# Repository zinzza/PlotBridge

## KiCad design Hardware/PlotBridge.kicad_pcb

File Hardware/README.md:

# PlotBridge — KiCad 프로젝트

ESP32-C3 SuperMini · ST7789 1.69" LCD · MAX3232(4핀) 모듈을 얹는 **캐리어 보드**다.
세 모듈 모두 완제품을 헤더에 꽂는 구조라 이 기판에는 능동소자가 없다.

보드는 **70 × 45 mm, 2층, 배선 완료** 상태다. ERC·DRC 모두 0건이다.

## 파일

| 파일 | 내용 |
|---|---|
| `PlotBridge.kicad_pro` | 프로젝트 파일 — KiCad에서 이걸 연다 |
| `PlotBridge.kicad_sch` | 회로도 (심볼 내장, 외부 라이브러리 불필요) |
| `PlotBridge.kicad_pcb` | 보드 — 외곽 70×45 mm, 부품 배치, 넷, **배선 완료**, M3 홀 4개 |
| `PlotBridge-schematic.pdf` | 회로도 출력본 |
| `PlotBridge.kicad_sym` | 심볼 라이브러리 |
| `PlotBridge.pretty/` | 풋프린트 라이브러리 (`.kicad_mod` 4종) |
| `sym-lib-table` / `fp-lib-table` | 프로젝트 로컬 라이브러리 등록 |
| `tools/` | 이 프로젝트를 생성·검증한 스크립트 |

## 검증 결과

KiCad 10.0.5의 `kicad-cli` / `pcbnew`로 실제 실행한 결과다.

| 항목 | 결과 | 도구 |
|---|---|---|
| ERC (회로도) | **0 violations** | `kicad-cli sch erc` |
| DRC (보드) | **0 violations** | `kicad-cli pcb drc` |
| 미연결 패드 | **0** | 〃 |
| 보드 패드↔넷 vs 회로도 넷리스트 | 10/10 넷 일치 | `tools/verify_board.py` |
| 심볼 핀번호 ↔ 풋프린트 패드 위치 | 28/28 일치 | `tools/verify_fp.py` |
| 같은 층 다른 넷 교차(단락) | **0** | `tools/verify_cross.py` |

## 넷리스트

| 넷 | ESP32-C3 | 상대 | 배선층 |
|---|---|---|---|
| `+3V3` | 3V3 (pin 6) | LCD VCC, MAX3232 VCC | B.Cu |
| `GND` | GND (pin 7) | LCD GND, MAX3232 GND | B.Cu |
| `LCD_SCL` | GPIO4 | LCD SCL | B.Cu |
| `LCD_SDA` | GPIO6 | LCD SDA | F.Cu |
| `LCD_RST` | GPIO1 | LCD RES | F.Cu |
| `LCD_DC` | GPIO3 | LCD DC | B.Cu |
| `LCD_CS` | GPIO2 | LCD CS | B.Cu |
| `LCD_BL` | GPIO5 | LCD BLK | B.Cu |
| `UART_TX` | GPIO0 | MAX3232 RX | B.Cu |
| `UART_RX` | GPIO7 | MAX3232 TX | F.Cu |

미사용: `5V`, `GPIO10`, `GPIO20`, `GPIO21` (no-connect 처리).
`GPIO8`(내장 LED), `GPIO9`(BOOT 버튼)는 모듈 온보드라 기판에서 연결하지 않는다.

## 배치와 배선

| 부품 | 위치 | 방향 |
|---|---|---|
| U1 ESP32-C3 SuperMini | (45, 47.5) | 세로, USB-C가 위 |
| U2 ST7789 LCD | (70, 47.5) | 세로 8핀, U1 오른쪽 |
| U3 MAX3232 | (45, 63) | **가로 4핀, U1 아래** (90° 회전) |
| H1–H4 M3 홀 | 네 모서리 | — |

U3는 왼쪽부터 `VCC(41.19) · GND(43.73) · RX(46.27) · TX(48.81)` 순으로 놓인다.

B.Cu가 주 배선층이다 — 모듈 본체가 윗면에 있어 아랫면이 통째로 비어 있고,
U1의 두 패드 열 사이 공간도 양면 모두 자유롭게 쓸 수 있다. 서로 교차하는
3개 넷(`LCD_SDA`, `LCD_RST`, `UART_RX`)만 F.Cu로 올렸다. 관통(THT) 패드가
양면을 잇기 때문에 **비아는 하나도 없다.** 트랙 폭 0.25 mm.

---

# 설계 노트

작업하면서 실제로 확인하거나 판단한 것들을 남긴다.

## ESP32-C3 SuperMini 핀 배치 — 가장 주의할 점

풋프린트는 **윗면(부품면) 기준, USB-C가 −Y 방향**이다. 이 기준에서 **전원핀은 오른쪽**이다.

| 왼쪽 열 (위→아래) | 오른쪽 열 (위→아래) |
|---|---|
| GPIO5, 6, 7, 8, 9, 10, 20, 21 | 5V, GND, 3V3, GPIO4, 3, 2, 1, 0 |

웹에 널리 퍼진 **"전원이 왼쪽"** 핀아웃 그림은 **뒷면(bottom) 뷰**가 앞면으로 잘못
재배포된 것이다. 이 그림을 그대로 믿고 기판을 뜨면 좌우가 뒤집힌 보드가 나온다.

실물 확인법(10초): USB-C를 위로 두고 칩이 보이는 면에서, 아래쪽 실크에
**왼쪽 `21` / 오른쪽 `0`** 이 찍혀 있으면 맞다.

근거는 세 갈래다.
- 독립 KiCad 라이브러리 6종이 모두 같은 배치(패드 좌표에 신호명이 직접 박혀 있어 해석 여지 없음)
- 실물 보드 실크스크린 사진
- Tenstar(AliExpress) 구매품 실물 확인

## 빨강/파랑 선이 겹쳐 보이는데 괜찮은가

괜찮다. 빨강은 `F.Cu`(윗면 동박), 파랑은 `B.Cu`(아랫면 동박)이고 사이에는
**1.6 mm 두께의 FR4 기판**이 있다. 도면에서 겹쳐 보이는 건 위에서 내려다본
투영일 뿐, 실제로는 육교와 그 아래 도로처럼 만나지 않는다. 2층 기판을 쓰는 이유가
바로 이것이다.

문제가 되는 건 **같은 층에서 다른 넷이 교차**하는 경우다. `tools/verify_cross.py`가
트랙 42개의 모든 쌍을 계산해 분류한다.

| 분류 | 개수 | |
|---|---|---|
| F.Cu ↔ B.Cu 교차 | 13 | 다른 층 — 무해 |
| 같은 층, 같은 넷 접촉 | 32 | 의도된 것 (모서리·분기) |
| **같은 층, 다른 넷 교차** | **0** | 단락 없음 |
| **같은 층, 다른 넷 간격 0.2 mm 미만** | **0** | 규칙 위반 없음 |

## 2층이면 1층보다 비싼가

**아니다. 소량에서는 오히려 2층이 더 싸거나 같다.**

요즘 PCB 업체의 표준 제품이 양면(2층)이다. 단면(1층)은 별도 옵션으로 없거나, 있어도
같은 값이거나, 비표준 공정이라 더 비싸다. 단가표의 기준 가격 자체가 2층이다.

단면이 실제로 싸지는 건 **수천 장 단위 양산**에서 FR-1/CEM-1 같은 저가 기판재를
쓸 때다. 리모컨이나 저가 완구 기판이 그 경우다. 시제품 5~10장에는 해당 없다.

이 보드는 70 × 45 mm라 대부분 업체의 최저가 구간(100 × 100 mm 이하)에 넉넉히 들어간다.

굳이 1층으로 내리려면 F.Cu를 쓰는 3개 넷(`LCD_SDA`, `LCD_RST`, `UART_RX`)을
점퍼선이나 0옴 저항으로 공중 배선해야 한다. 가격 이득 없이 조립 수고와 실수 여지만
늘어나므로 권하지 않는다.

## 수작업 납땜이 가능한가

가능하다. 난이도로 치면 가장 쉬운 축이다.

**층수는 납땜 난이도와 무관하다.** 층수는 제조사가 하는 일이고, 난이도를 좌우하는 건
부품 패키지와 패드 크기다. 오히려 공장에서 만든 2층 기판은 홀 내벽에 구리가 도금되어
나오므로(PTH, plated through-hole), **한쪽 면만 납땜해도 납이 구멍을 타고 올라가
양쪽 층이 자동으로 연결**된다. 윗면에 따로 손댈 필요가 없다.
(집에서 직접 에칭한 2층 기판이라면 양면 납땜이 필요하지만, 발주 기판은 해당 없다.)

| 항목 | 값 | 평가 |
|---|---|---|
| 부품 | 전부 THT (핀헤더) | SMD 0개 |
| 패드 지름 | 1.8 mm | 넉넉함 |
| 드릴 | 1.0 mm | 2.54 mm 헤더 핀(0.64 mm 각)에 여유 |
| 애뉼러 링 | 0.4 mm | 인두 팁 닿을 면적 충분 |
| 인접 패드 간격 | 0.74 mm | 브리지 위험 낮음 |
| 납땜할 핀 | 28개 (16+8+4) | — |

### 조립 순서

1. **암 헤더(female header)를 기판에 먼저 납땜한다.** 모듈이 올라가면 인두가 안 들어간다.
2. 납땜은 **아랫면(B.Cu)에서만** 하면 된다.
3. 모듈 3개를 나중에 꽂는다.

암 헤더를 쓰면 모듈을 뺐다 꽂을 수 있다. MAX3232 핀 순서가 다른 제품으로 바꿔야 할
때를 대비해서도 소켓 방식이 안전하다.

인두는 320~350 °C에 핀당 2~3초면 충분하다.

## KiCad와 EasyEDA

둘 다 무료로 시작할 수 있지만 성격이 다르다.

| | KiCad | EasyEDA |
|---|---|---|
| 라이선스 | 완전 무료·오픈소스(GPL), 기능 제한 없음 | 웹 버전 무료, 비공개 프로젝트 개수 제한 |
| 유료 등급 | 없음 | EasyEDA Pro (데스크톱) |
| 강점 | 어느 제조사에나 통하는 범용 거버 출력 | JLCPCB 부품 소싱·주문 연동 |

이 프로젝트는 KiCad를 골랐다. 국내 업체(devicemart 등)에 거버로 넘기기에 무난하고,
특정 제조사 생태계에 묶이지 않기 때문이다.

## PCB 발주에 필요한 것

발주 페이지가 요구하는 건 배선도(개념 회로도)가 아니라 실제 동박 패턴이 담긴
**거버(Gerber) 파일**과 드릴 파일이다. `Docs/wiring_diagram.html`은 연결 관계를
보여주는 문서일 뿐 발주용이 아니다.

```bash
kicad-cli pcb export gerbers --output gerber/ PlotBridge.kicad_pcb
kicad-cli pcb export drill   --output gerber/ PlotBridge.kicad_pcb
```

---

# 제작 전 확인 사항

1. **MAX3232 모듈의 핀 순서를 실물로 확인한다.** 4핀 모듈은 판매자마다 순서가 다르다.
   현재 풋프린트는 `VCC, GND, RX, TX` (pin 1 = VCC) 기준이다.
2. MAX3232 모듈이 **3.3V VCC**를 지원하는지 확인한다. 5V 전용이면 레벨 변환이 필요하다.
3. RS-232 측은 모듈의 DB9 커넥터를 쓴다. 이 기판에는 RS-232 신호가 올라오지 않는다.
   플로터 연결은 교차: MAX3232 TX → 플로터 RX, MAX3232 RX ← 플로터 TX.
4. LCD 모듈의 8핀 순서(`GND VCC SCL SDA RES DC CS BLK`)도 실물 실크와 대조한다.
5. LCD(1.69")와 MAX3232 모듈의 **실제 외형이 서로 간섭하지 않는지** 확인한다.
   현재 배치는 헤더 간격만 기준이며 모듈 본체 크기는 반영하지 않았다.

---

# 재생성

`tools/gen_kicad.py`가 회로도·보드·라이브러리를 전부 생성한다. 배치나 배선을 바꾸려면
스크립트의 `PLACE` / `ROUTES`를 고치고 다시 돌린다.

`tools/normalize_pcb.py`는 KiCad 자체 엔진(`pcbnew`)으로 보드의 모든 풋프린트를
라이브러리에서 다시 불러와 같은 자리에 재배치한다. 손으로 쓴 사본은 부품을 **회전**시키는
순간 라이브러리와 어긋나므로(KiCad는 풋프린트 텍스트 각도를 보드 절대각으로 저장한다)
이 단계가 없으면 DRC가 `lib_footprint_mismatch`를 낸다. KiCad 번들 파이썬으로 돌린다.

```bash
python tools/gen_kicad.py
"C:/Program Files/KiCad/10.0/bin/python.exe" tools/normalize_pcb.py
python tools/verify_net.py && python tools/verify_fp.py && python tools/verify_board.py
python tools/verify_cross.py
```

검증기는 서로 독립적이다.

| 스크립트 | 확인하는 것 |
|---|---|
| `verify_net.py` | 회로도 기하학에서 넷리스트를 재구성해 의도와 대조 |
| `verify_fp.py` | 심볼 핀번호 ↔ 풋프린트 패드 물리 위치 |
| `verify_board.py` | 보드의 패드↔넷이 회로도와 일치하는지 |
| `verify_cross.py` | 같은 층에서 다른 넷이 닿는 곳이 있는지 |

DRC는 보드가 "자기모순이 없음"만 보장하지 "맞다"는 것은 보장하지 않는다. 넷을 잘못
할당해도 DRC는 통과한다. 그래서 위 대조가 따로 필요하다.

> **주의:** 재생성은 `.kicad_sch` / `.kicad_pcb`를 덮어쓴다. KiCad에서 프로젝트를 열어둔
> 상태로 돌렸다면, KiCad를 닫았다가 다시 열어야 새 내용이 보인다. 열린 창에서 저장하면
> 재생성한 내용이 지워진다.

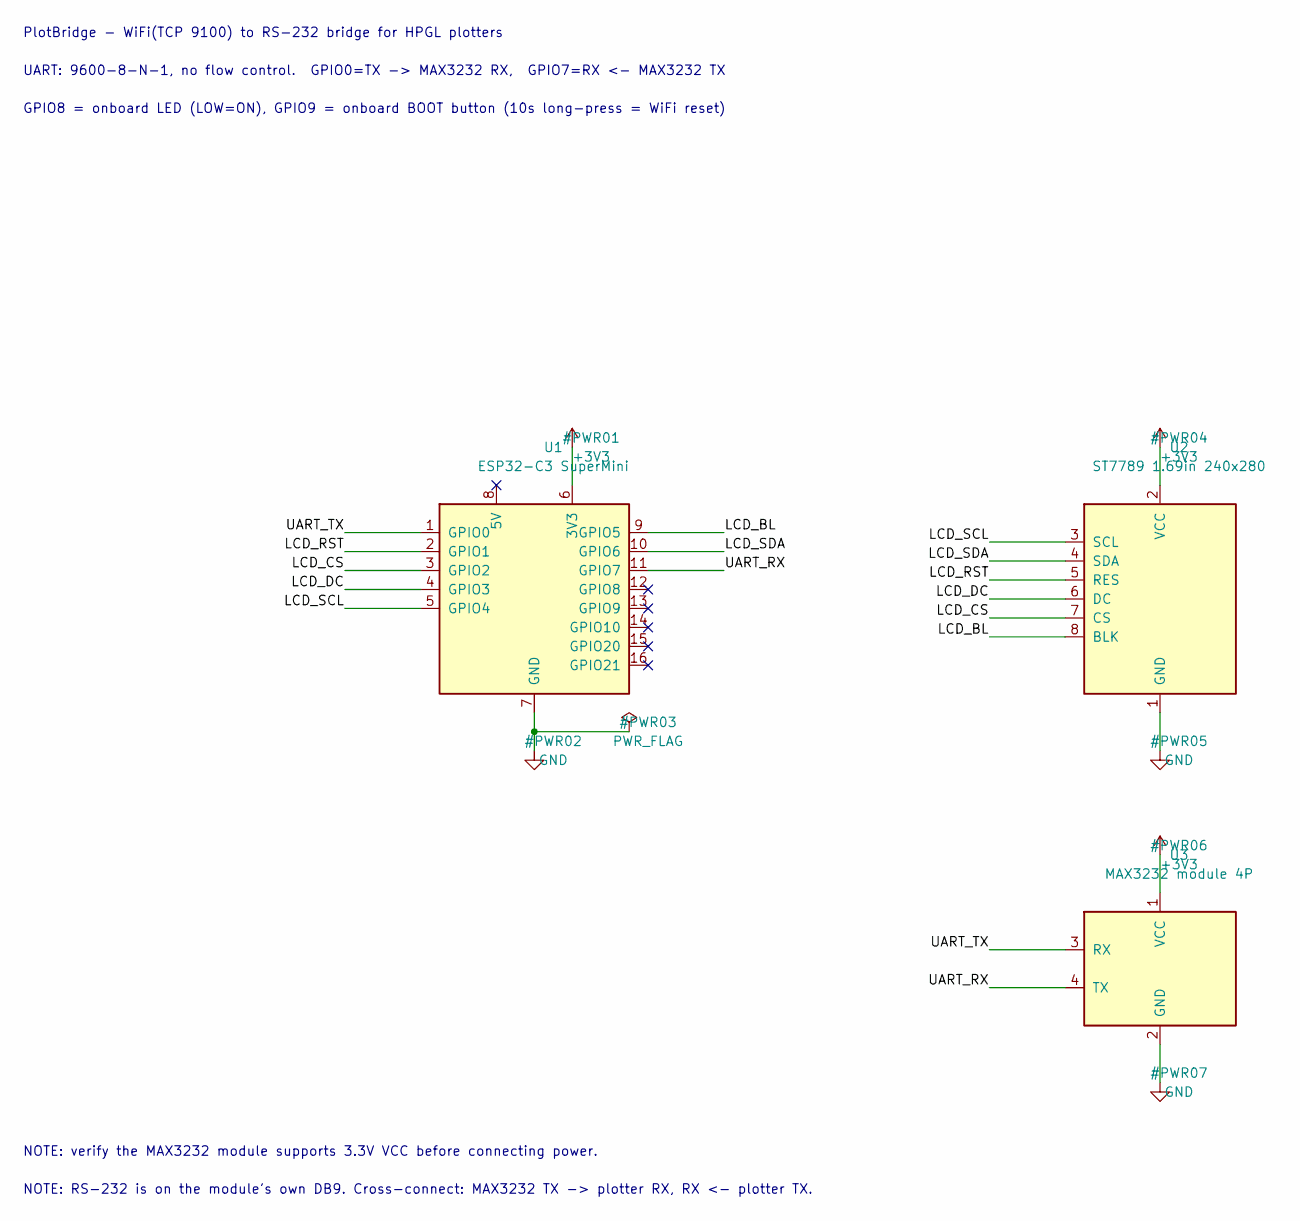
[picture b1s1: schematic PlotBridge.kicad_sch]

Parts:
U1: ESP32-C3 SuperMini; ESP32-C3_SuperMini
U2: ST7789 1.69in 240x280; ST7789_169_8P
U3: MAX3232 module 4P; MAX3232_MODULE_4P

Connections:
+3V3: U1.6 (3V3), U2.2 (VCC), U3.1 (VCC)
GND: U1.7 (GND), U2.1 (GND), U3.2 (GND)
LCD_BL: U1.9 (GPIO5), U2.8 (BLK)
LCD_CS: U1.3 (GPIO2), U2.7 (CS)
LCD_DC: U1.4 (GPIO3), U2.6 (DC)
LCD_RST: U1.2 (GPIO1), U2.5 (RES)
LCD_SCL: U1.5 (GPIO4), U2.3 (SCL)
LCD_SDA: U1.10 (GPIO6), U2.4 (SDA)
UART_RX: U1.11 (GPIO7), U3.4 (TX)
UART_TX: U1.1 (GPIO0), U3.3 (RX)

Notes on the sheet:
PlotBridge - WiFi(TCP 9100) to RS-232 bridge for HPGL plotters
UART: 9600-8-N-1, no flow control. GPIO0=TX -> MAX3232 RX, GPIO7=RX <- MAX3232 TX
GPIO8 = onboard LED (LOW=ON), GPIO9 = onboard BOOT button (10s long-press = WiFi reset)
NOTE: verify the MAX3232 module supports 3.3V VCC before connecting power.
NOTE: RS-232 is on the module's own DB9. Cross-connect: MAX3232 TX -> plotter RX, RX <- plotter TX.

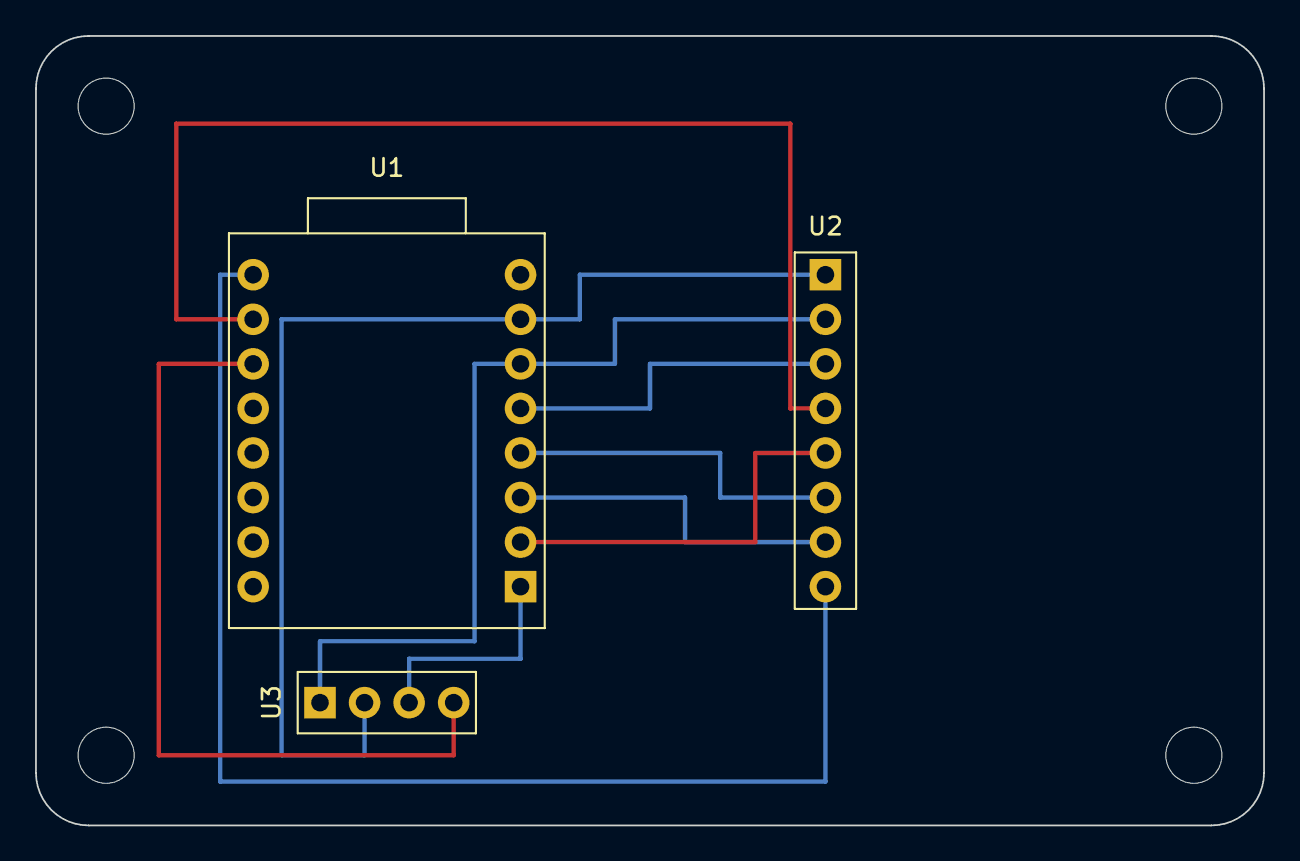
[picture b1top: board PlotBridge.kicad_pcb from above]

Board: 2 copper layers, 70.0 x 45.0 mm, 7 parts (0 on the bottom side), 10 nets.

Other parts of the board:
H1, H2, H3, H4: MountingHole_M3

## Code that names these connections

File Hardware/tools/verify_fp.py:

# -*- coding: utf-8 -*-
"""Cross-check: symbol pin number -> signal name  vs  footprint pad number -> physical position.
Ground truth = the board pinout the user confirmed physically (power on the RIGHT, top view)."""
import os, collections
from verify_net import tokenize, parse, val, find_all, find_one   # reuse parser

HW = r"C:\Projects\Arduino\PlotBridge\Hardware"

# ---- ground truth, top view, USB-C at top (-Y). Confirmed against the physical board.
TRUTH = {
  "ESP32-C3_SuperMini": {
    "right": ["5V", "GND", "3V3", "GPIO4", "GPIO3", "GPIO2", "GPIO1", "GPIO0"],
    "left":  ["GPIO5", "GPIO6", "GPIO7", "GPIO8", "GPIO9", "GPIO10", "GPIO20", "GPIO21"],
  },
  # single-row modules: order as printed on the module, pin 1 first
  "ST7789_169_8P":     {"single": ["GND", "VCC", "SCL", "SDA", "RES", "DC", "CS", "BLK"]},
  "MAX3232_MODULE_4P": {"single": ["VCC", "GND", "RX", "TX"]},
}

# ---- symbol: number -> name
sym_map = {}
lib = parse(tokenize(open(os.path.join(HW, "PlotBridge.kicad_sym"), encoding="utf-8").read()))[0]
for sym in find_all(lib, "symbol"):
    name = val(sym[1]).split(":")[-1]
    m = {}
    for sub in find_all(sym, "symbol"):
        for p in find_all(sub, "pin"):
            m[val(find_one(p, "number")[1])] = val(find_one(p, "name")[1])
    if m:
        sym_map[name] = m

# ---- footprint: number -> (x, y)
fp_map = {}
for fn in sorted(os.listdir(os.path.join(HW, "PlotBridge.pretty"))):
    fp = parse(tokenize(open(os.path.join(HW, "PlotBridge.pretty", fn), encoding="utf-8").read()))[0]
    name = val(fp[1])
    pads = {}
    for pad in find_all(fp, "pad"):
        at = find_one(pad, "at")
        pads[val(pad[1])] = (float(val(at[1])), float(val(at[2])))
    fp_map[name] = pads

problems = []
for part, truth in TRUTH.items():
    print("=" * 66)
    print(part)
    print("=" * 66)
    s, f = sym_map[part], fp_map[part]
    if set(s) != set(f):
        problems.append("%s: symbol pins %s != footprint pads %s"
                        % (part, sorted(set(s) - set(f)), sorted(set(f) - set(s))))
        continue
    cols = collections.defaultdict(list)
    for num, (x, y) in f.items():
        cols[x].append((y, num))
    if "single" in truth:
        want = {min(cols): truth["single"]}
    else:
        want = {max(cols): truth["right"], min(cols): truth["left"]}
    for x, order in want.items():
        got = [num for _, num in sorted(cols[x])]          # top -> bottom
        print("  x=%+7.2f  top->bottom" % x)
        for i, num in enumerate(got):
            sig, exp = s[num], order[i] if i < len(order) else "??"
            ok = sig == exp
            print("     pad %-3s  symbol=%-7s expected=%-7s %s" % (num, sig, exp, "ok" if ok else "MISMATCH"))
            if not ok:
                problems.append("%s pad %s: symbol says %s, board says %s" % (part, num, sig, exp))
    print()

print("=" * 66)
if problems:
    print("PROBLEMS (%d):" % len(problems))
    for p in problems:
        print("   -", p)
else:
    print("RESULT: symbol pin numbers and footprint pad positions agree with the physical board")
